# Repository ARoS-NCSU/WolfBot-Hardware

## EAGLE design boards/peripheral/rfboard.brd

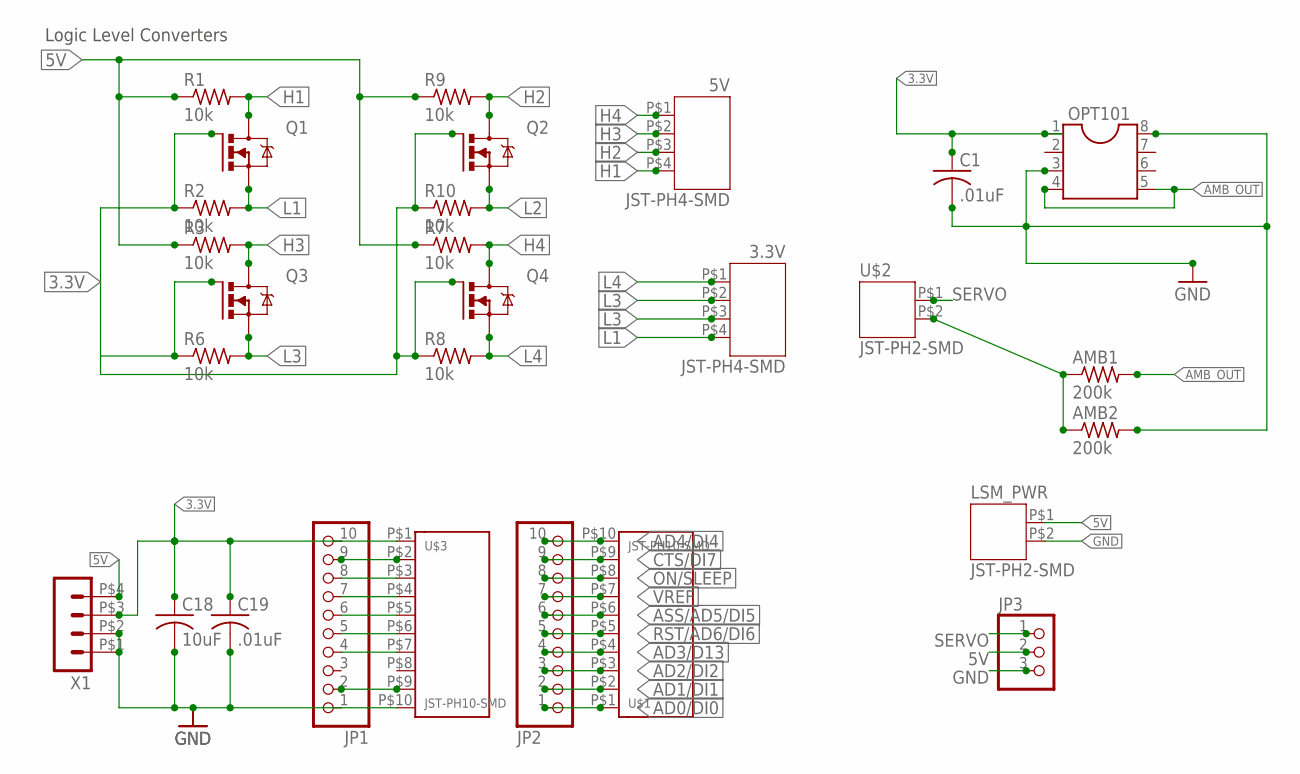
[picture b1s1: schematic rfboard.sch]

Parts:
3.3V, 5V: JST-PH4-SMD
AMB1, AMB2: 200k; R0805
C1, C19: .01uF; C0805K
C18: 10uF; C1206K
JP1, JP2: PINHD-1X10_2.00; 1X10M
JP3: PINHD-1X3; 1X03
LSM_PWR: JST-PH2-SMD
OPT101: DIL8; DIL08
Q1, Q2, Q3, Q4: IRLML5203; MICRO3
R1, R2, R3, R6, R7, R8, R9, R10: 10k; R0805
U$1, U$3: JST-PH10-SMD
U$2: JST-PH2-SMD
X1: HEADER_POS4_43045-0406; 43045-0406

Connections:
3.3V: C1.1, C18.1, C19.1, JP1.10, OPT101.1, Q1.1 (G), Q2.1 (G), Q3.1 (G), Q4.1 (G), R2.1, R6.1, R8.1, R10.1, U$3.P$1, X1.P$3 (3)
5V: JP3.2, LSM_PWR.P$1 (1), R1.1, R3.1, R7.1, R9.1, X1.P$4 (4)
AD0/DI0: JP2.1, U$1.P$1
AD1/DI1: JP2.2, U$1.P$2
AD2/DI2: JP2.3, U$1.P$3
AD3/D13: JP2.4, U$1.P$4
AD4/DI4: JP2.10, U$1.P$10
AMB_LOW: AMB1.1, AMB2.1, U$2.P$2 (2)
AMB_OUT: AMB1.2, OPT101.4, OPT101.5
ASS/AD5/DI5: JP2.6, U$1.P$6
CTS/DI7: JP2.9, U$1.P$9
DIN/CONFIG: JP1.8, U$3.P$3
DO8: JP1.7, U$3.P$4
DOUT: JP1.9, U$3.P$2
DTR/SLEEP_RQ/D18: JP1.2, U$3.P$9
GND: AMB2.2, C1.2, C18.2, C19.2, JP1.1, JP3.3, LSM_PWR.P$2 (2), OPT101.3, OPT101.8, U$3.P$10, X1.P$1 (1), X1.P$2 (2)
H1: 5V.P$4 (4), Q1.3 (D), R1.2
H2: 5V.P$3 (3), Q2.3 (D), R9.2
H3: 5V.P$2 (2), Q3.3 (D), R3.2
H4: 5V.P$1 (1), Q4.3 (D), R7.2
L1: 3.3V.P$4 (4), Q1.2 (S), R2.2
L2: 3.3V.P$3 (3), Q2.2 (S), R10.2
L3: 3.3V.P$2 (2), Q3.2 (S), R6.2
L4: 3.3V.P$1 (1), Q4.2 (S), R8.2
ON/SLEEP: JP2.8, U$1.P$8
PWM0/RSSI: JP1.5, U$3.P$6
PWM1: JP1.4, U$3.P$7
RESET: JP1.6, U$3.P$5
RST/AD6/DI6: JP2.5, U$1.P$5
SERVO: JP3.1, U$2.P$1 (1)
VREF: JP2.7, U$1.P$7

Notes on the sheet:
Logic Level Converters

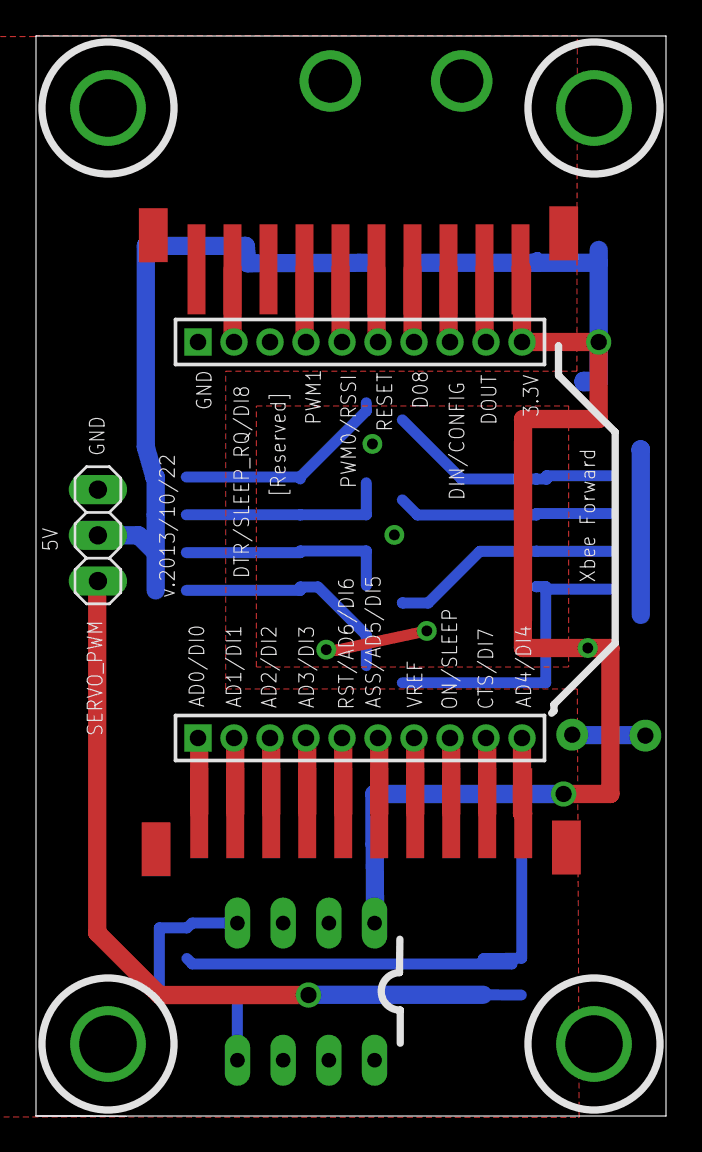
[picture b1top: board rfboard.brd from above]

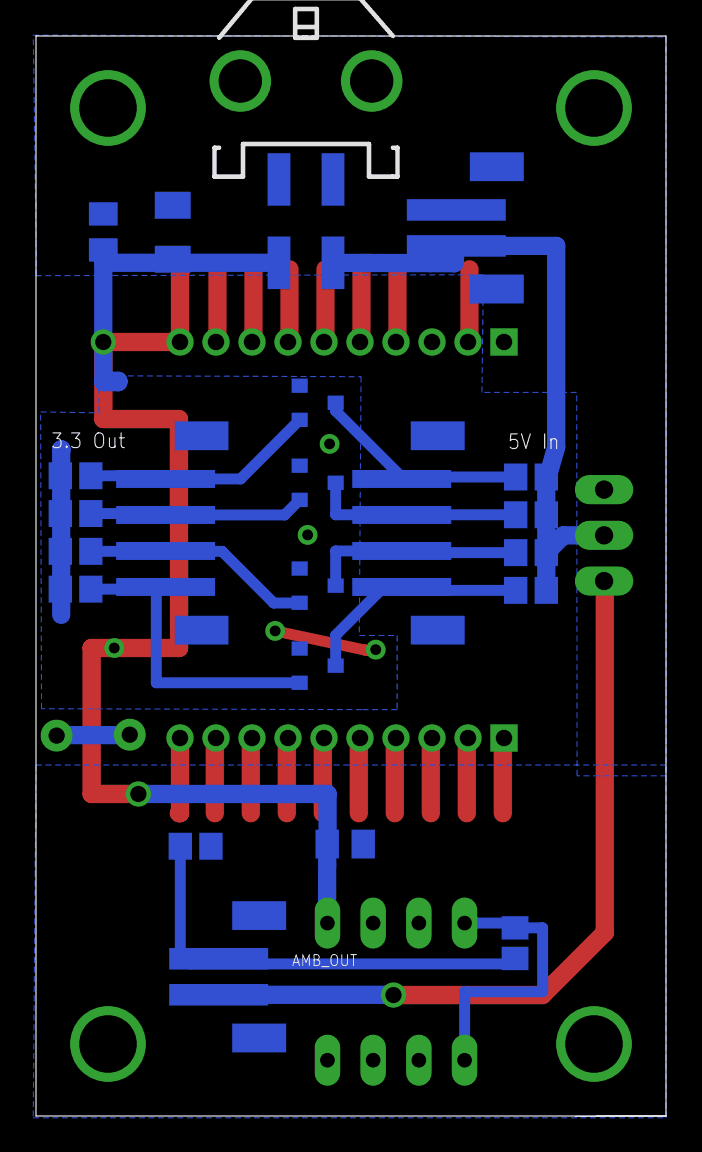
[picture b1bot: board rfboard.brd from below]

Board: 2 copper layers, 35.0 x 60.0 mm, 28 parts (22 on the bottom side), 31 nets.

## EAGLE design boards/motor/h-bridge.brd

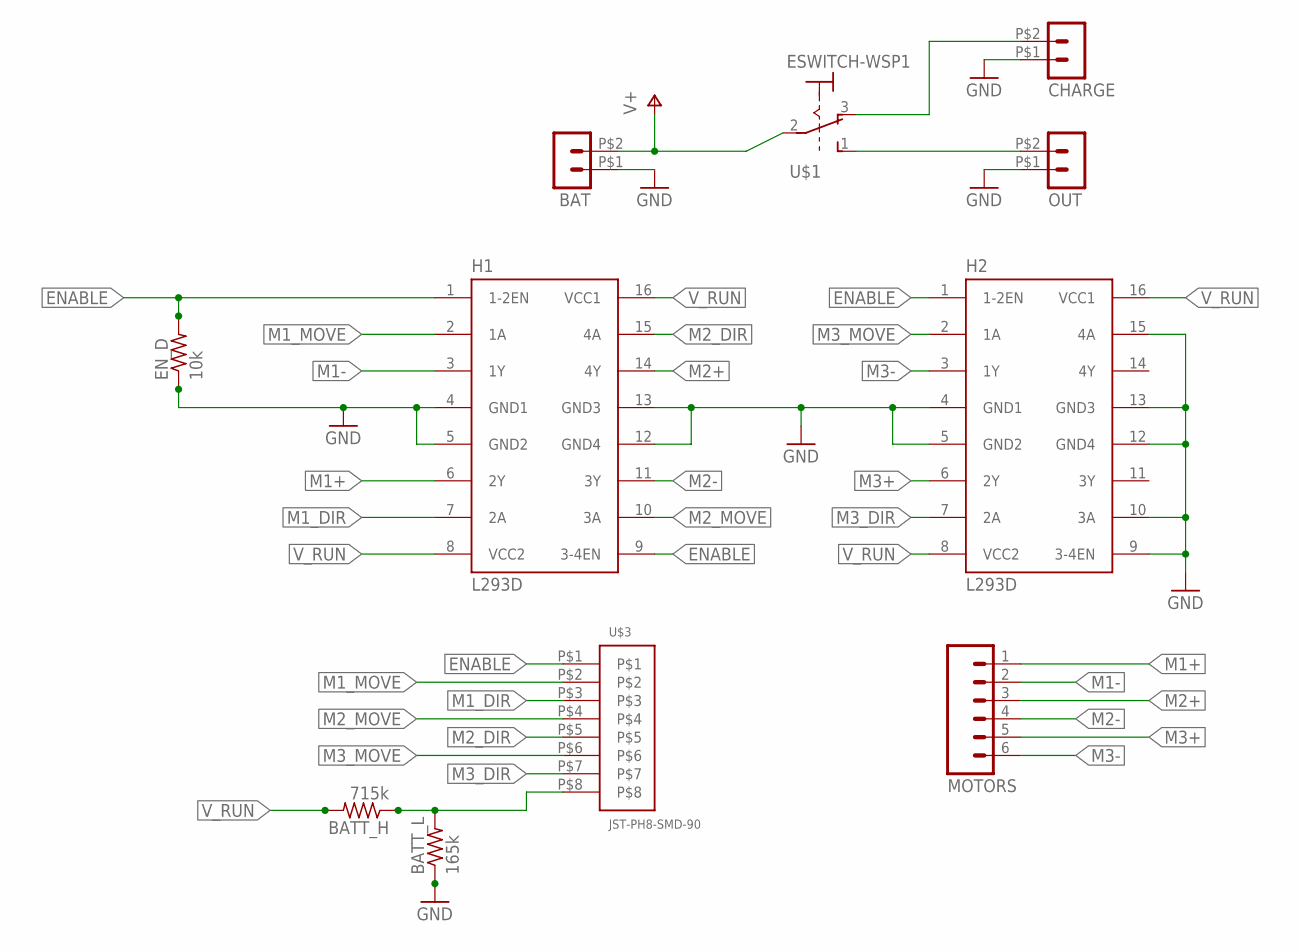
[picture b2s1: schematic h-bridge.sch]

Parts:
BAT: HEADER_POS2_43045-0206; 43045-0206
BATT_H: 715k; R0805
BATT_L: 165k; R0805
CHARGE: HEADER_POS2_43045-0206; 43045-0206
EN_D: 10k; R0805
H1, H2: L293D; DIL16
MOTORS: M06LOCK; 1X06_LOCK
OUT: HEADER_POS2_43045-0206; 43045-0206
U$1: ESWITCH-WSP1; WSP1-T2-M6
U$3: JST-PH8-SMD-90; JST-PH-SMD-90*

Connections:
ENABLE: EN_D.2, H1.1 (1-2EN), H1.9 (3-4EN), H2.1 (1-2EN), U$3.P$1
GND: BAT.P$1 (1), BATT_L.1, CHARGE.P$1 (1), EN_D.1, H1.4 (GND1), H1.5 (GND2), H1.12 (GND4), H1.13 (GND3), H2.4 (GND1), H2.5 (GND2), H2.9 (3-4EN), H2.10 (3A), H2.12 (GND4), H2.13 (GND3), H2.15 (4A), OUT.P$1 (1)
M1+: H1.6 (2Y), MOTORS.1
M1-: H1.3 (1Y), MOTORS.2
M1_DIR: H1.7 (2A), U$3.P$3
M1_MOVE: H1.2 (1A), U$3.P$2
M2+: H1.14 (4Y), MOTORS.3
M2-: H1.11 (3Y), MOTORS.4
M2_DIR: H1.15 (4A), U$3.P$5
M2_MOVE: H1.10 (3A), U$3.P$4
M3+: H2.6 (2Y), MOTORS.5
M3-: H2.3 (1Y), MOTORS.6
M3_DIR: H2.7 (2A), U$3.P$7
M3_MOVE: H2.2 (1A), U$3.P$6
unnamed: BATT_H.1, BATT_L.2, U$3.P$8
V+: BAT.P$2 (2), U$1.2
V_CHARGE: CHARGE.P$2 (2), U$1.3
V_RUN: BATT_H.2, H1.8 (VCC2), H1.16 (VCC1), H2.8 (VCC2), H2.16 (VCC1), OUT.P$2 (2), U$1.1

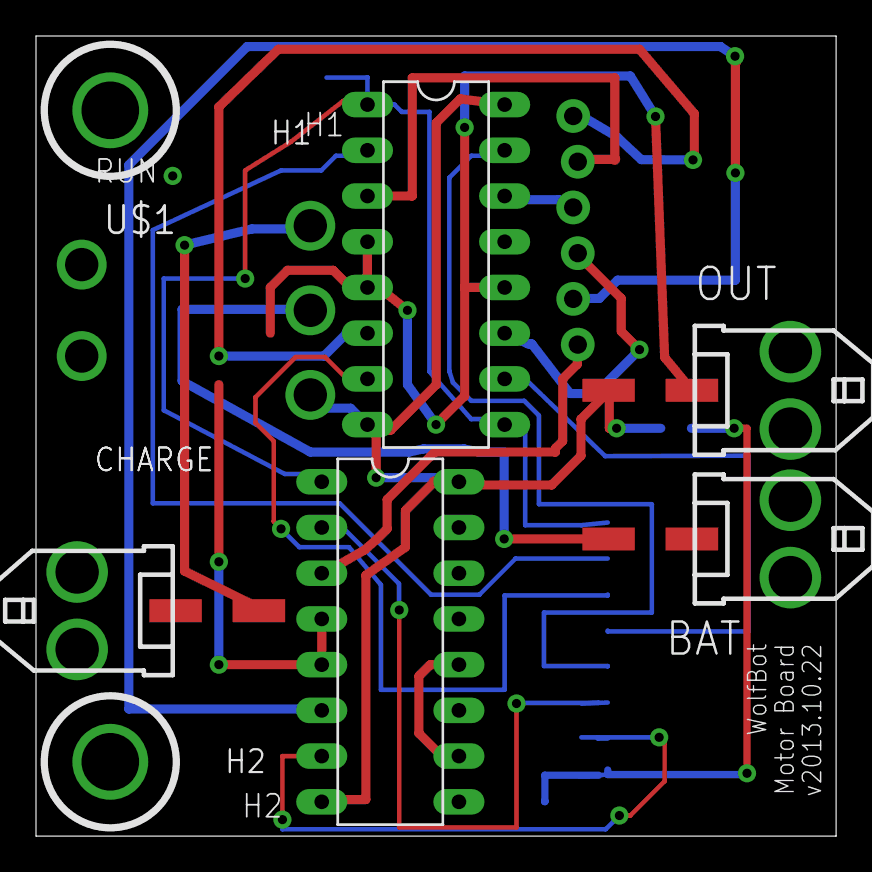
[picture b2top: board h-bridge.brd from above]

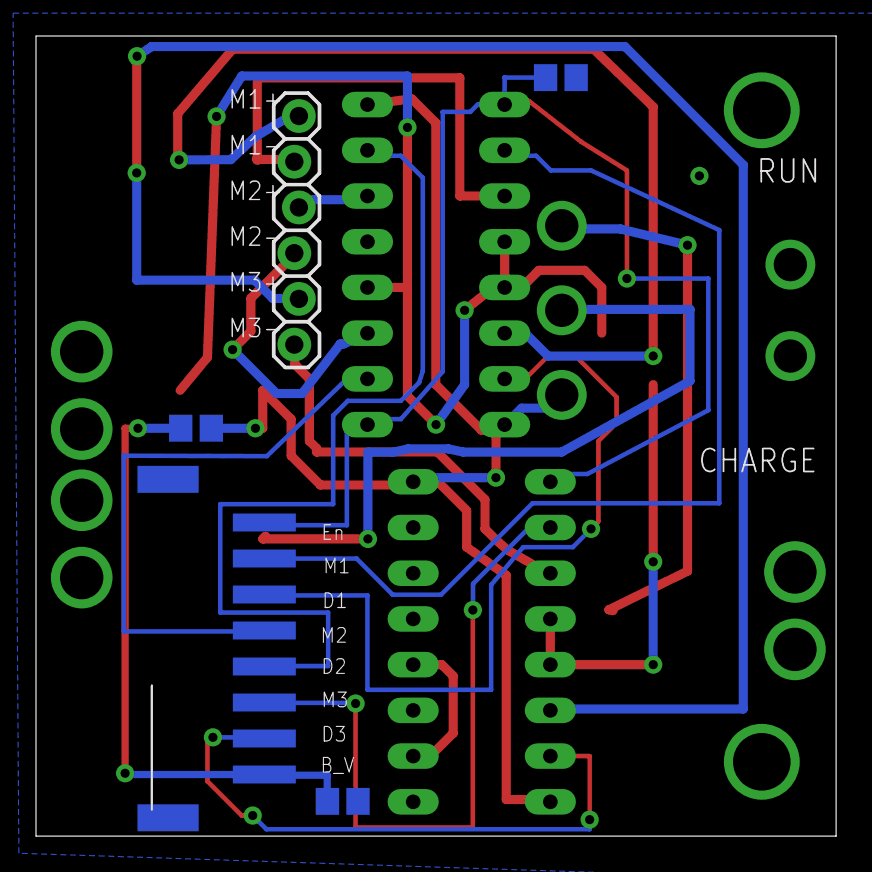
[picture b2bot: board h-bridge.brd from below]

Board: 2 copper layers, 44.5 x 44.5 mm, 11 parts (5 on the bottom side), 18 nets.

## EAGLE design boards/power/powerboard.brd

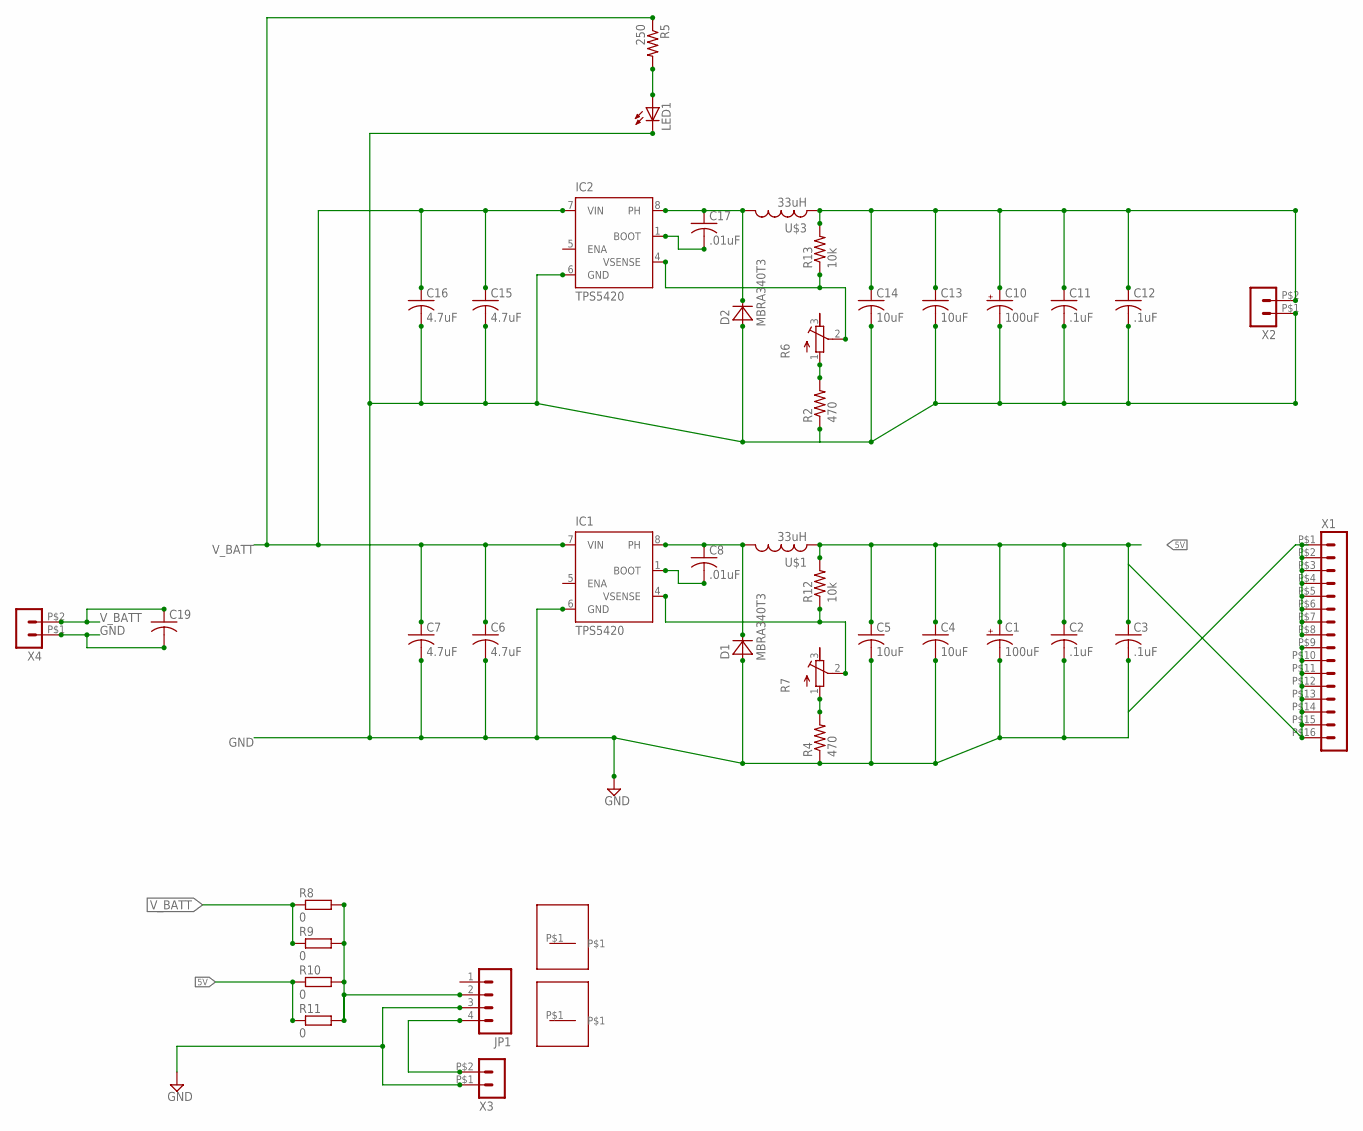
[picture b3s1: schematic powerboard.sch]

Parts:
C1, C10: 100uF; C/6032-28R
C2, C3, C11, C12: .1uF; C1206K
C4, C5, C13, C14: 10uF; C1206K
C6, C7, C15, C16: 4.7uF; C1812K
C8, C17: .01uF; C0805K
C19: C-USC2220K; C2220K
D1, D2: MBRA340T3; SMA
IC1, IC2: TPS5420; D_R-PDSO-G08
JP1: M04LOCK; 1X04_LOCK
LED1: LEDSML1206; SML1206
R2, R4: 470; R3216
R5: 250; R1206
R6, R7: R-TRIMM3224W; RTRIM3224W
R8, R9, R10, R11: 0; R0805
R12, R13: 10k; M0805
U$1, U$3: 33uH; MSS1260
U$2, U$4: THERMAL_PAD
X1: HEADER_POS16_43045-1606; 43045-1606
X2, X3, X4: HEADER_POS2_43045-0206; 43045-0206

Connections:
3_3V: C10.+, C11.1, C12.1, C13.1, C14.1, R13.2, U$3.P$2, U$3.P$4, X2.P$2 (2)
5V: C1.+, C2.1, C3.1, C4.1, C5.1, R10.1, R11.1, R12.2, U$1.P$2, U$1.P$4, X1.P$9 (9), X1.P$10 (10), X1.P$11 (11), X1.P$12 (12), X1.P$13 (13), X1.P$14 (14), X1.P$15 (15), X1.P$16 (16)
6VOUT: JP1.4, X3.P$2 (2)
GND: C1.-, C2.2, C3.2, C4.2, C5.2, C6.2, C7.2, C10.-, C11.2, C12.2, C13.2, C14.2, C15.2, C16.2, C19.2, D1.A, D2.A, IC1.6 (GND), IC2.6 (GND), JP1.3, LED1.C, R2.1, R4.1, X1.P$1 (1), X1.P$2 (2), X1.P$3 (3), X1.P$4 (4), X1.P$5 (5), X1.P$6 (6), X1.P$7 (7), X1.P$8 (8), X2.P$1 (1), X3.P$1 (1), X4.P$1 (1)
unnamed: C8.2, IC1.1 (BOOT)
unnamed: IC1.4 (VSENSE), R7.2 (S), R12.1
unnamed: C8.1, D1.C, IC1.8 (PH), U$1.P$1, U$1.P$3
unnamed: C17.2, IC2.1 (BOOT)
unnamed: IC2.4 (VSENSE), R6.2 (S), R13.1
unnamed: C17.1, D2.C, IC2.8 (PH), U$3.P$1, U$3.P$3
unnamed: LED1.A, R5.2
unnamed: R2.2, R6.1 (A)
unnamed: R4.2, R7.1 (A)
VIN: JP1.2, R8.2, R9.2, R10.2, R11.2
V_BATT: C6.1, C7.1, C15.1, C16.1, C19.1, IC1.7 (VIN), IC2.7 (VIN), R5.1, R8.1, R9.1, X4.P$2 (2)

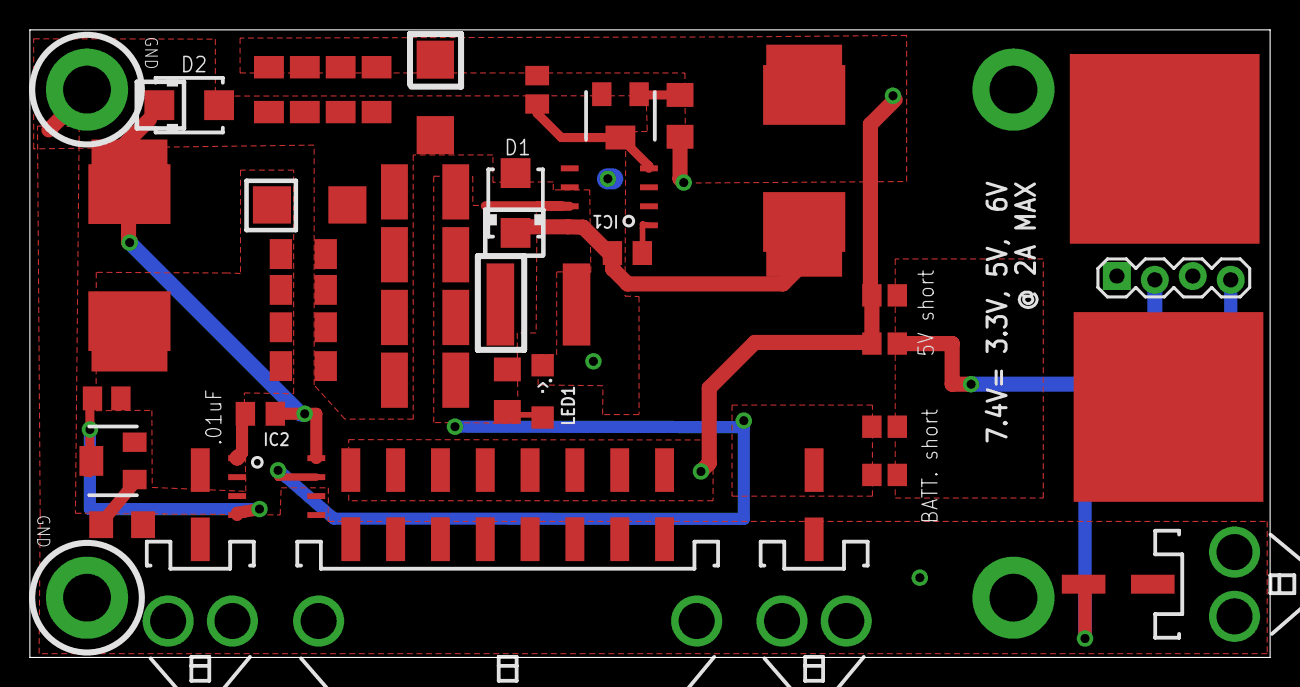
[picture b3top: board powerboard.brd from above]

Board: 2 copper layers, 83.0 x 42.0 mm, 42 parts (0 on the bottom side), 15 nets.

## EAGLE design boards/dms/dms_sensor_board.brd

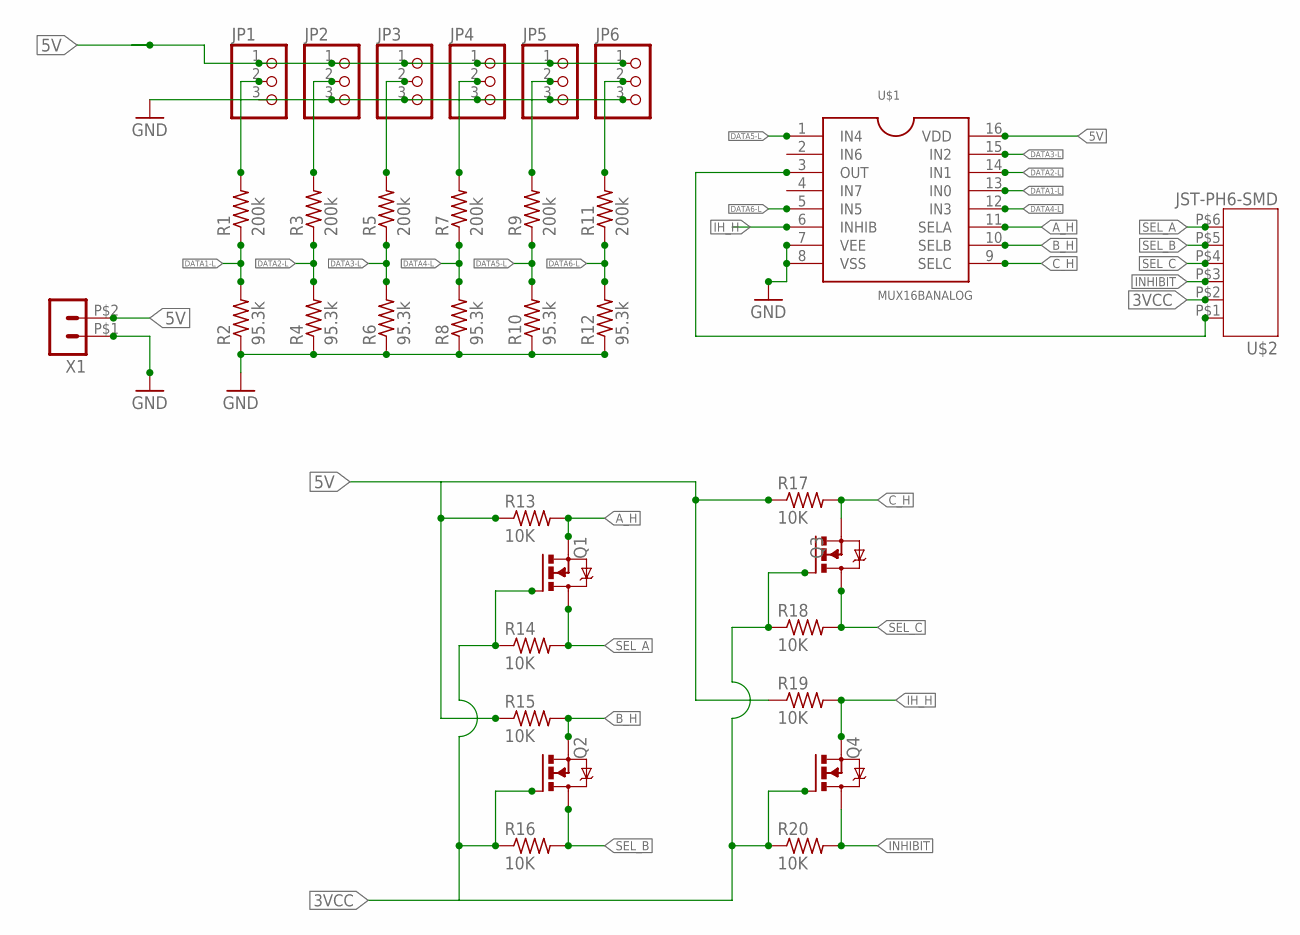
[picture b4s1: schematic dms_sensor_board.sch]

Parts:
JP1, JP2, JP3, JP4, JP5, JP6: PINHD-1X03_2.00; 1X03M
Q1, Q2, Q3, Q4: IRLML5203; MICRO3
R1, R3, R5, R7, R9, R11: 200k; R0805
R2, R4, R6, R8, R10, R12: 95.3k; R0805
R13, R14, R15, R16, R17, R18, R19, R20: 10K; R0805
U$1: MUX16BANALOG; SO16
U$2: JST-PH6-SMD
X1: HEADER_POS2_43045-0206; 43045-0206

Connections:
3VCC: Q1.1 (G), Q2.1 (G), Q3.1 (G), Q4.1 (G), R14.1, R16.1, R18.1, R20.1, U$2.P$2 (2)
5V: JP1.1, JP2.1, JP3.1, JP4.1, JP5.1, JP6.1, R13.1, R15.1, R17.1, R19.1, U$1.16 (VDD), X1.P$2 (2)
A_H: Q1.2 (S), R13.2, U$1.11 (SELA)
B_H: Q2.2 (S), R15.2, U$1.10 (SELB)
C_H: Q3.2 (S), R17.2, U$1.9 (SELC)
DATA1-H: JP1.2, R1.2
DATA1-L: R1.1, R2.2, U$1.13 (IN0)
DATA2-H: JP2.2, R3.2
DATA2-L: R3.1, R4.2, U$1.14 (IN1)
DATA3-H: JP3.2, R5.2
DATA3-L: R5.1, R6.2, U$1.15 (IN2)
DATA4-H: JP4.2, R7.2
DATA4-L: R7.1, R8.2, U$1.12 (IN3)
DATA5-H: JP5.2, R9.2
DATA5-L: R9.1, R10.2, U$1.1 (IN4)
DATA6-H: JP6.2, R11.2
DATA6-L: R11.1, R12.2, U$1.5 (IN5)
GND: JP1.3, JP2.3, JP3.3, JP4.3, JP5.3, JP6.3, R2.1, R4.1, R6.1, R8.1, R10.1, R12.1, U$1.7 (VEE), U$1.8 (VSS), X1.P$1 (1)
IH_H: Q4.2 (S), R19.2, U$1.6 (INHIB)
INHIBIT: Q4.3 (D), R20.2, U$2.P$3 (3)
unnamed: U$1.3 (OUT), U$2.P$1 (1)
SEL_A: Q1.3 (D), R14.2, U$2.P$6 (6)
SEL_B: Q2.3 (D), R16.2, U$2.P$5 (5)
SEL_C: Q3.3 (D), R18.2, U$2.P$4 (4)

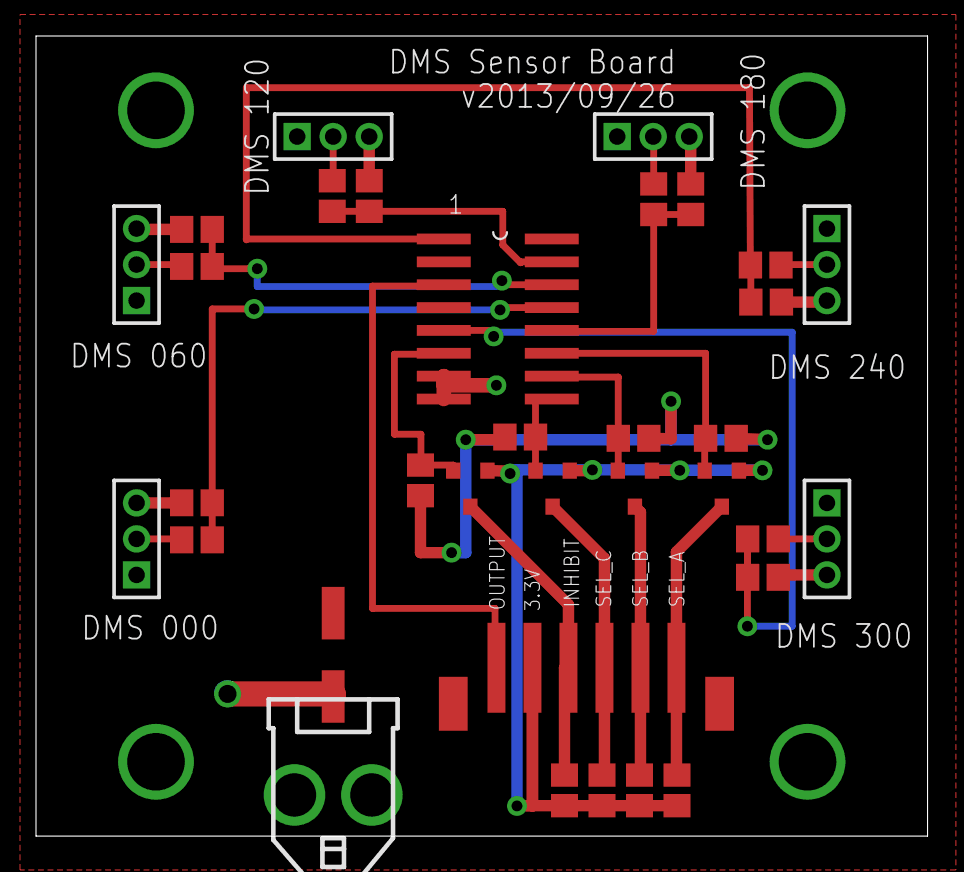
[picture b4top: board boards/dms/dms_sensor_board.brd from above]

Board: 2 copper layers, 49.5 x 44.5 mm, 33 parts (0 on the bottom side), 24 nets.

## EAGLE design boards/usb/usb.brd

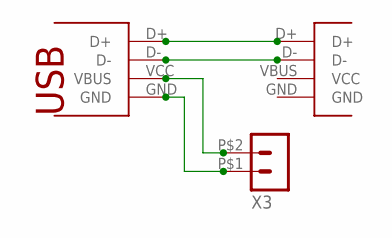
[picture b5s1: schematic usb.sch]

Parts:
U$1: USB-A_FEM; USB-A-S
U$2: USB-A-PLUG; USB-A-H
X3: HEADER_POS2_43045-0206; 43045-0206

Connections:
D+: U$1.D+, U$2.D+
D-: U$1.D-, U$2.D-
GND: U$1.GND, X3.P$1 (1)
VCC: U$1.VCC (VBUS), X3.P$2 (2)

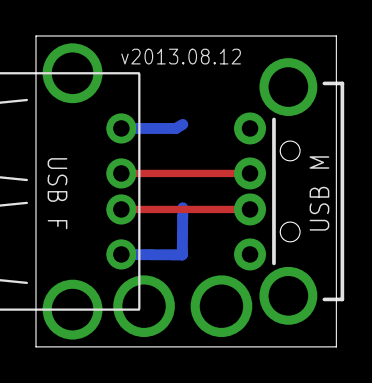
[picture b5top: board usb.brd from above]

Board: 2 copper layers, 16.7 x 17.3 mm, 3 parts (1 on the bottom side), 4 nets.

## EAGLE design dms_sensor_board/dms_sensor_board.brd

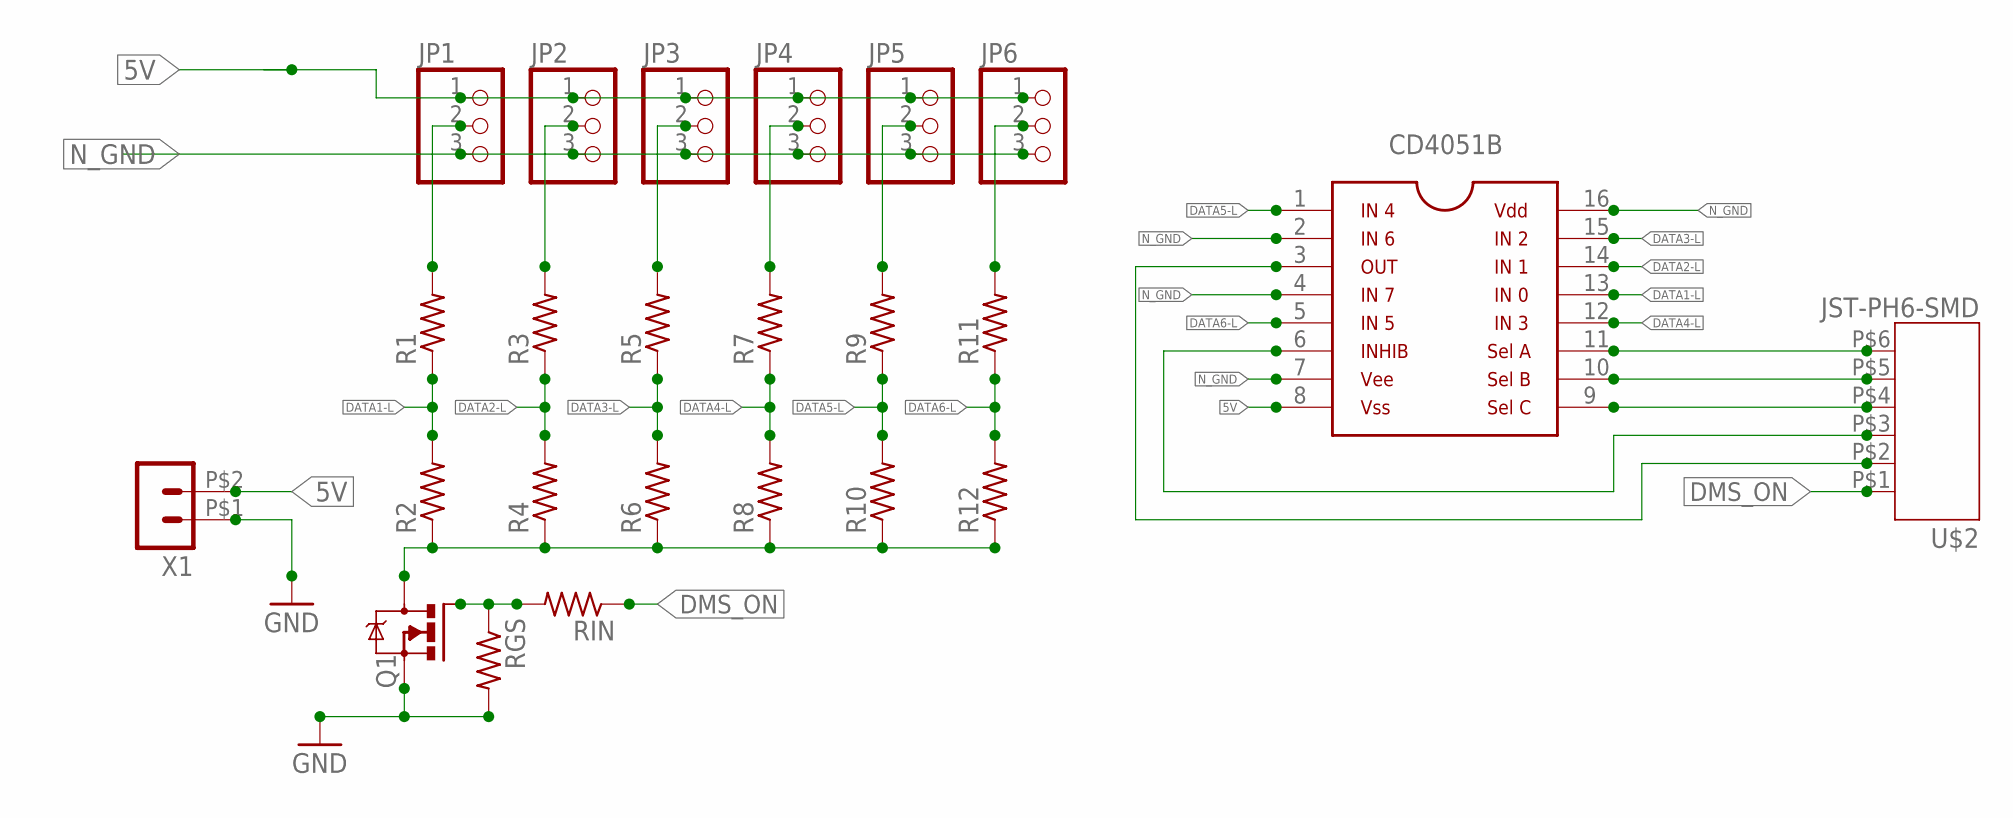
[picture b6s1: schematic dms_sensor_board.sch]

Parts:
JP1, JP2, JP3, JP4, JP5, JP6: PINHD-1X03_2.00; 1X03M
MUX1: 8X1; SO16
Q1: IRLML5203; MICRO3
R1, R2, R3, R4, R5, R6, R7, R8, R9, R10, R11, R12: R-US_R0805; R0805
RGS: R-US_R0805; R0805
RIN: R-US_R0805; R0805
U$2: JST-PH6-SMD
X1: HEADER_POS2_43045-0206; 43045-0206

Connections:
5V: JP1.1, JP2.1, JP3.1, JP4.1, JP5.1, JP6.1, MUX1.8, X1.P$2 (2)
DATA1-H: JP1.2, R1.2
DATA1-L: MUX1.13, R1.1, R2.2
DATA2-H: JP2.2, R3.2
DATA2-L: MUX1.14, R3.1, R4.2
DATA3-H: JP3.2, R5.2
DATA3-L: MUX1.15, R5.1, R6.2
DATA4-H: JP4.2, R7.2
DATA4-L: MUX1.12, R7.1, R8.2
DATA5-H: JP5.2, R9.2
DATA5-L: MUX1.1, R9.1, R10.2
DATA6-H: JP6.2, R11.2
DATA6-L: MUX1.5, R11.1, R12.2
DMS_ON: RIN.1, U$2.P$1 (1)
GND: Q1.3 (S), RGS.2, X1.P$1 (1)
unnamed: MUX1.11, U$2.P$6 (6)
unnamed: MUX1.10, U$2.P$5 (5)
unnamed: MUX1.9, U$2.P$4 (4)
unnamed: MUX1.6, U$2.P$3 (3)
unnamed: MUX1.3, U$2.P$2 (2)
unnamed: Q1.1 (G), RGS.1, RIN.2
N_GND: JP1.3, JP2.3, JP3.3, JP4.3, JP5.3, JP6.3, MUX1.2, MUX1.4, MUX1.7, MUX1.16, Q1.2 (D), R2.1, R4.1, R6.1, R8.1, R10.1, R12.1

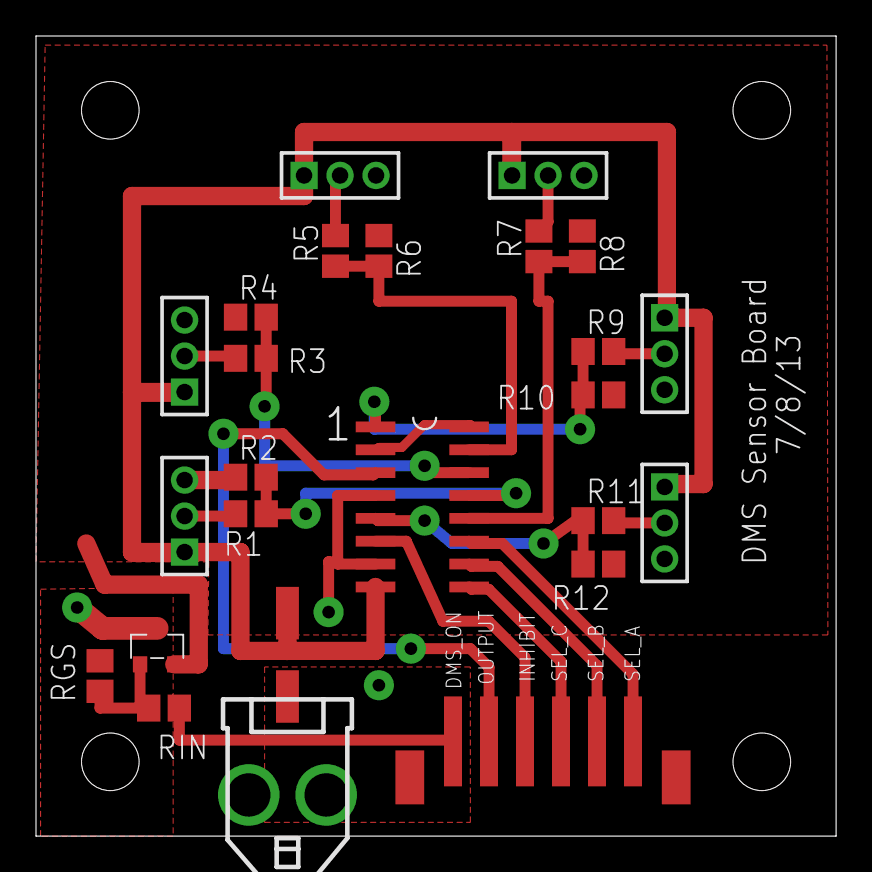
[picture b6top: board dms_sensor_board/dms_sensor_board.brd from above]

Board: 2 copper layers, 44.5 x 44.5 mm, 24 parts (0 on the bottom side), 22 nets.

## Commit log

2013-05-27 Initial revision of H-bridge schematic and board
    - current switch does not use the correct footprint
    - drill holes have not been verified
2013-05-28 Rework H-bridge to add charge port, move headers to back
    - correct hole sizes and placement
    - added key dimension documentation
    - switch toggles battery between circuit and charge port
    - headers on backside leading toward center of chassis
    - battery in and daisy chain output also point into center
2013-05-28 Fix V_RUN net so that it is actually attached to ICs
2013-05-29 test commit
2013-05-30 Add WolfBot Eagle library
    - only includes E-Switch WSP1 toggle switch for now
2013-05-30 Update H-bridge board to use correct switch
    - The E-switch WSP1 is a custom model from the wolfbot.lbr library
    - Shifted most components due to the larger switch footprint
2013-05-31 Commit of original RF/peripheral board Eagle files
2013-05-31 changing the RF board to include voltage dividers
    - rearranged board to include pin headers
2013-05-31 changed headers and finished board
2013-05-31 created the zip for the gerber files
2013-05-31 Gerber files for RFboard
2013-05-31 Gerber zip file instructions
2013-05-31 Standard Eagle PCB construction instructions
2013-06-01 Reroute H-bridge board for conservative design rules
    - 20 mil drill holes
    - 20 mil power traces with 20 mil clearance
2013-06-01 Cosmetic updates to h-bridge board
    - change fonts to vector
    - add board identifier and version string
2013-06-02 Add Eagle configruation files for DRC and CAM
    - SparkFun DRU, which should be sufficiently conservative
    - gerber_excellon: CAM used for previous boards
    - gerber_excellon_no_names: same as above, without tNames/bNames
    - script to generate zip file of gerbers ready for manufacture
2013-06-02 Makefile for gerber zip, git ignore many Eagle files
    - ignore backup files
    - ignore zips
    - ignore info files
    - ignore gerbers
2013-06-05 Changes to layout and silk screen, new gerber files
2013-06-05 corrected silk screen
2013-06-05 Neal's custom gerber files, which use tsilk and bsilk layers
2013-06-05 Daniel's gerber file cam job.
2013-06-05 ignoring extraneous eagle files
2013-06-05 cleaning up working directory
2013-06-05 added version label
2013-06-05 Cam changes for gerbmerger
2013-06-06 Add missing stop mask to rfboard vias
2013-06-06 Update description for "no names" CAM job.
2013-06-06 Panelization configuration for motor and peripheral boards
    - three row panelization using gerbmerge (7 of each board)
    - add border to "no names" CAM job
    - fix ngohara CAM job to use RS274X device for border
2013-06-06 Fix type on gitmerge config, add .gitignore
2013-06-09 added ambient light sensor and 3 voltage dividers, new XBEE connection
    -added the MONOLITHIC PHOTODIODE AND SINGLE-SUPPLY TRANSIMPEDANCE AMPLIFIER, ie OPT101 abmient light sensors
    -added circuitry for the OPT101
    -added header pin, labeled AMB_OUT, for the output of the OPT101
    -added three extra voltage dividers for future DMS sensors
    -added six 2mm 2pin headers for the DMS Sensors cables
    --NOTE: the DMS sensor headers are currently GND, VCC, DATA from left to right
2013-06-09 created powerboard repository
2013-06-18 I believe these are close to the Powerboard's design for 3.3V and 5V
    I made this using TI's WEBENCH software
2013-06-18 New boost design for 6Volt rail
    I made this using TI's WEBENCH software. The LM3488 is the voltage stepper chip used.
2013-06-18 A look at a 12volt rail. Not in use as of this commit.
2013-06-18 Added the 6volt rail to schematic. Board not done.
2013-06-22 Flipped board on side to fit within EagleLite's size limits
2013-06-22 Deleted TP1 and TP2 (test points) because they seem useless
    -Moved parts around to reduce footprint
2013-06-24 Finished layout of power board with 6V.
    -Does not include new connectors for 3.3 and 5v rail yet
2013-06-28 changing XBee pinout, and adding logic converters
2013-06-29 changing logic converters and pinout
2013-07-03 deleted AND circuit from RF board
2013-07-03 small change in rf circuit
2013-07-03 created basic six dms sensor circuit
2013-07-03 added 8b mux and started pcb
2013-07-03 added mosfet control over DMS ON
2013-07-03 Finished dms sensor board layout, needs DRC
2013-07-03 Added 2nd 56uF cap to powerboard, finished, needs DRC
2013-07-04 Deleted voltage dividers, modified pinout
2013-07-05 added voltage div to Amb_out, and amb_on fet
2013-07-05 finished laying board with components on bottom
2013-07-08 Fixed DMS_on fet with resistors and finished text
2013-07-08 Fixed fet Amb_On with resistors, fixed connector orientation, fixed text
2013-07-08 fixed fet, and fixed connector type
2013-07-09 add connector parts
2013-07-09 tested and fixed until passed Sparkfun's DRC
2013-07-10 resolved Sparkfun DRC errors, except for in-between pin errors
2013-07-10 changed gitignore to ignore cam files everywhere
2013-07-10 mostly silkscreen fixes
2013-07-10 specific cam file for current boards
2013-07-10 Clean up of Eagle files and related scripts
    - Consistent makefiles for all boards
    - CAM files renamed tweaked to produce only necessary gerbers
    - delete generated gerbers
    - rename powerboard
2013-07-10 Add border file generation to each CAM proflie
2013-07-11 hole size, wire distance fixes, no soldermask changes yet
2013-07-11 changed all vias, except screw holes, to stop mask on
2013-07-12 Fixed PH connector footprint and resistor in way
2013-07-12 Changed DMS holes to via to fix copper width error
2013-07-13 Move all PCB schematic/board files into subdirectory
2013-07-15 Initial commit of time sliced IR in Python
    - wolfbot class to hold configuration of individual bots
    - configuration files defining unique host ids and common IR parameters
    - slicer class provides time-slicing functionality
    - IR module for manipulating IR TX PWM and RX GPIO and pulse generation
2013-08-07 Changing boards for fet and text improvements
2013-08-08 changes for new boards, cleared DRC
2013-08-08 Move panelization config and update for all boards
2013-08-09 added documentation for new 6V rail
2013-08-09 fixed stopmask errors
2013-08-10 New board for plugin regulator
2013-08-10 text fixes
2013-08-10 Remove old panel definition file
2013-08-10 text change for V_batt resistors
2013-08-10 fixed improper ground issue
2013-08-12 Fix motor board silk screening
    - add tValues and bValues to CAM job
    - move resistor labels
    - remove unwanted labels
2013-08-13 made usb breakout board
2013-08-13 Reorganize USB board files, add makefile
2013-08-13 Minor tweaks to USB board: wider, silkscreen
    - wider so male USB can be moved in for better support
    - added version stamp and tweaked other silk
    - labeled signal lines in schematic
    - added dimension layer to top silk in CAM job
2013-08-13 Add USB board (x3) to full panel
2013-09-15 Fixed pull down, and three res sizes
2013-09-15 Fixed Mux padsize, cleared relavent DRC errors
2013-09-15 Fixed 470 cap footprint
2013-09-15 Added LED indicator
2013-09-26 Cleanup issues, working on powerboard res move
2013-09-26 moving pot
2013-09-26 finished powerboard changes
2013-09-26 changed resistors and fixed text
2013-09-27 fixed PRF labels
2013-10-04 This junk got changed somehow, is not anything I changed.
2013-10-21 changed size, moved holes, added servo header
2013-10-21 fixed via short problem
2013-10-22 Break signal between motor board mounting holes
2013-10-22 Update motor board version label
2013-10-22 Update PRF board version label
2013-10-29 Add wiring charts in SVG (and PDF generator)
2013-10-30 Wiring: Swap colors on multiple KRDs, extend servo power
2013-10-30 Wiring: extend PRF power lines slightly
2013-11-14 Mark III version of Wolfbot Solidworks Files
2013-11-14 Mark IV Version of Wolfbot.
2013-11-15 Wiring chart: extend BB to PB connector
2013-11-22 Construction Updates. Added media to Google Drive
2013-11-22 Images for Construction Wiki
2013-11-23 Remove assembly images that were moved to wiki repo
2014-02-19 Add OSH Park Eagle design rule file for Eagle
2014-02-19 Add SVG source for BBB P8/P9 connector label PDFs
2014-02-19 Ignore generated PDFs

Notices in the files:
parts and their libraries:
SparkFun-Connectors: Licensing: CC v3.0 Share-Alike You are welcome to use this library for commercial purposes.
